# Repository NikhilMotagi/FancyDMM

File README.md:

# FancyDMM

Inspired by the Atmega328P-based voltage and current measuring device utilizing the INA266 current sensor, I aim to create a more compact and cost-effective version using the versatile ATTiny microcontroller. 
This project will involve designing a circuit to measure both voltage and current, processing the data using the ATTiny, and displaying the results on an appropriate display.
To keep the code size low, I used Bare Metal coding. 
____
## Photo Gallery

|||
|-----|------|
|||

____
## Project Inspired from

link : <https://hackaday.io/project/191203-mini-oled-panel-meter>

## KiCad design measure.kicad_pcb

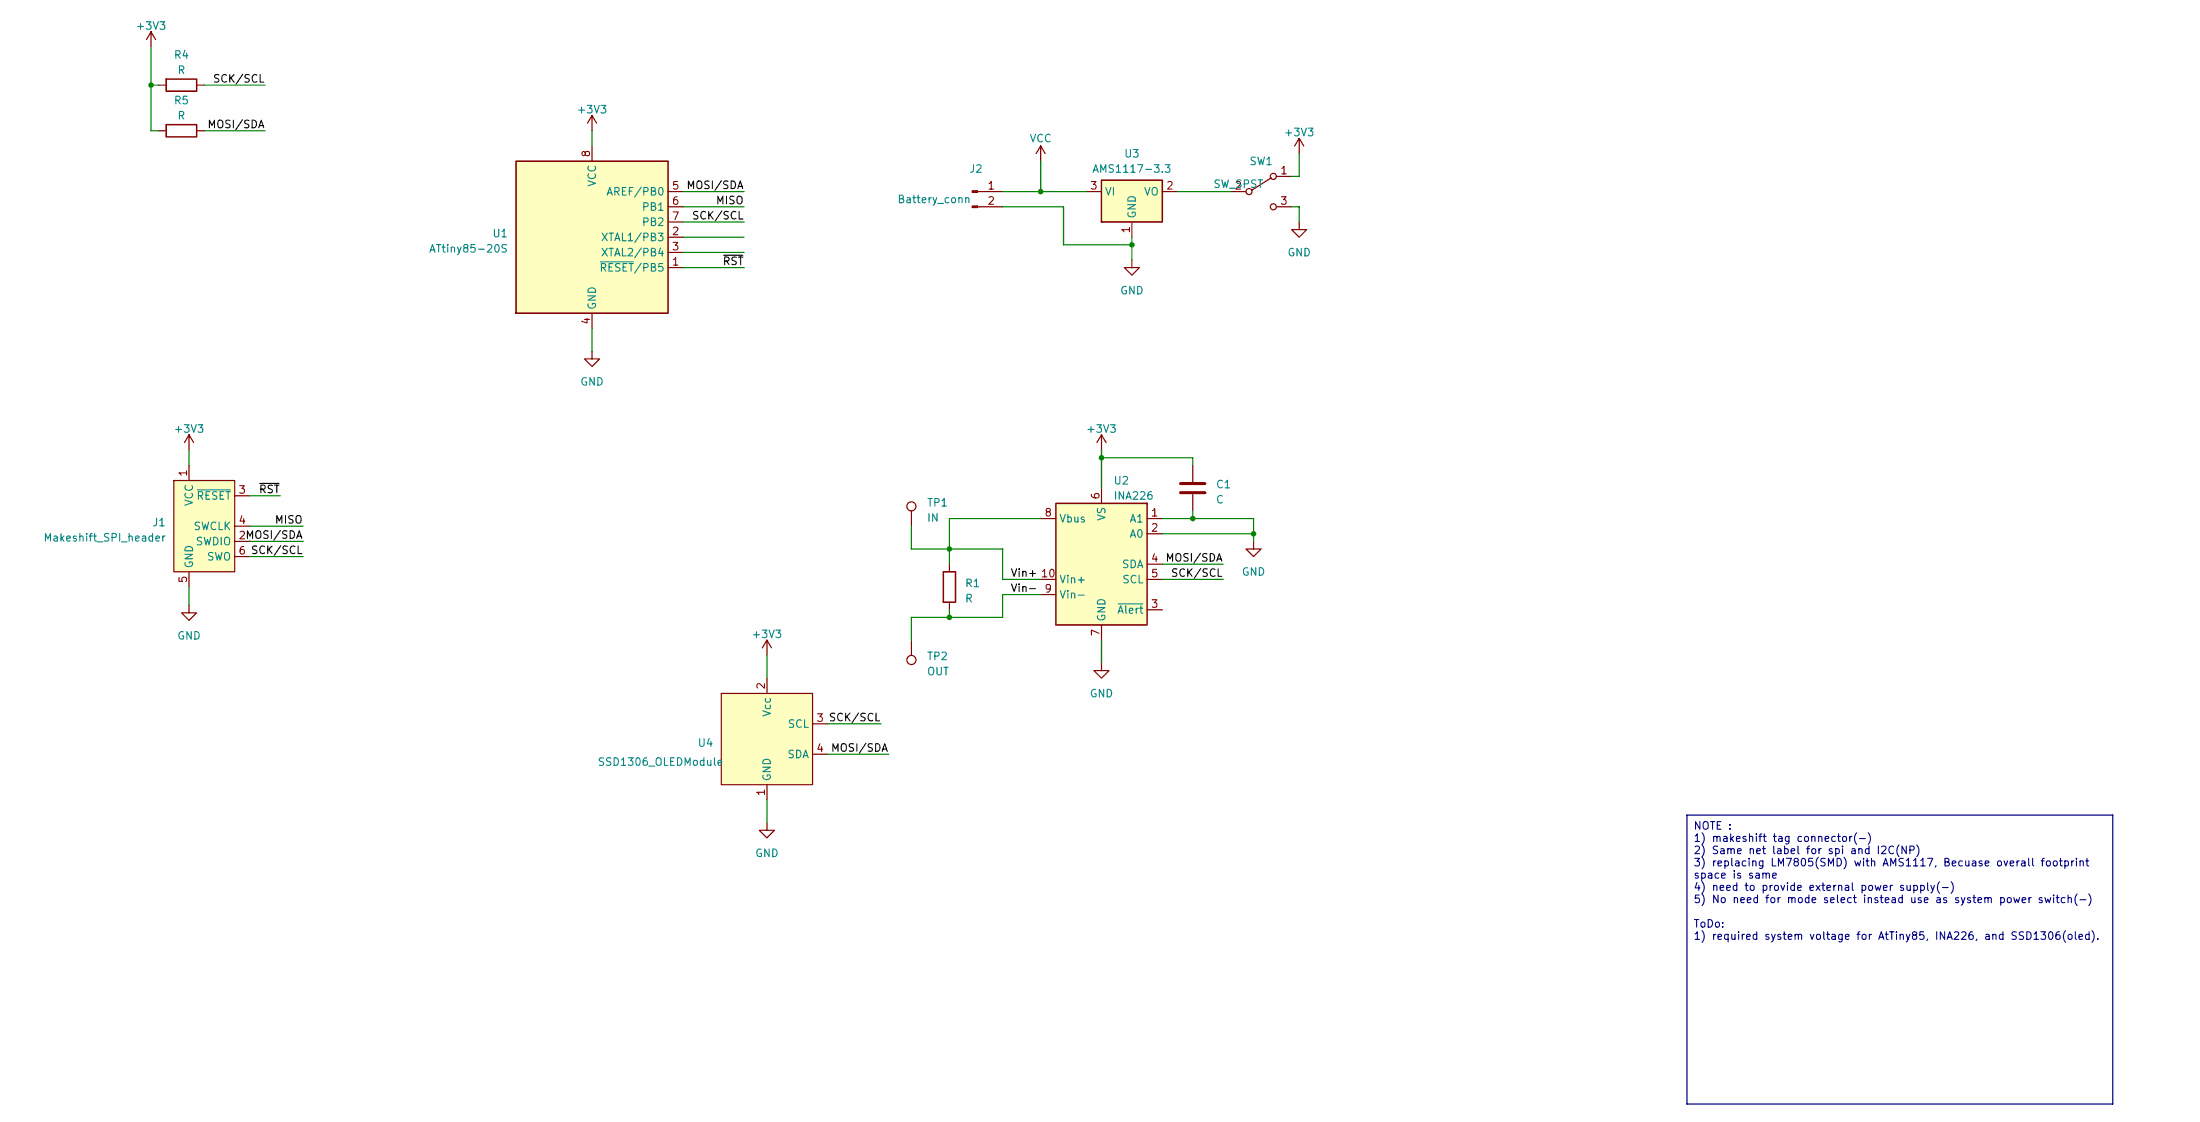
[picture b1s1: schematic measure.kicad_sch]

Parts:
C1: C; C_0805_2012Metric
J1: Makeshift_SPI_header; Tag-Connect_TC2030-IDC-NL_2x03_P1.27mm_Vertical
J2: Battery_conn; JST_GH_SM02B-GHS-TB_1x02-1MP_P1.25mm_Horizontal
R1: R; R_2512_6332Metric
R4, R5: R; R_0603_1608Metric
SW1: SW_SPST; SW_SPDT_CK-JS102011SAQN
TP1: IN; TestPoint_Pad_4.0x4.0mm
TP2: OUT; TestPoint_Pad_4.0x4.0mm
U1: ATtiny85-20S; SOIC-8W_5.3x5.3mm_P1.27mm
U2: INA226; VSSOP-10_3x3mm_P0.5mm
U3: AMS1117-3.3; SOT-223-3_TabPin2
U4: SSD1306_OLEDModule

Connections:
+3V3: C1.1, J1.1 (VCC), R4.2, R5.2, SW1.1 (A), U1.8 (VCC), U2.6 (VS), U4.2 (Vcc)
/MISO: J1.4 (SWCLK), U1.6 (PB1)
/MOSI/SDA: J1.2 (SWDIO), R5.1, U1.5 (AREF/PB0), U2.4 (SDA), U4.4 (SDA)
/SCK/SCL: J1.6 (SWO), R4.1, U1.7 (PB2), U2.5 (SCL), U4.3 (SCL)
/Vin+: R1.1, TP1.1, U2.8 (Vbus), U2.10 (Vin+)
/Vin-: R1.2, TP2.1, U2.9 (Vin-)
/~RST: J1.3 (~RESET), U1.1 (~RESET/PB5)
GND: C1.2, J1.5 (GND), J2.2, SW1.3 (C), U1.4 (GND), U2.1 (A1), U2.2 (A0), U2.7 (GND), U3.1 (GND), U4.1 (GND)
unnamed: SW1.2 (B), U3.2 (VO)
VCC: J2.1, U3.3 (VI)

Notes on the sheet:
NOTE : 1) makeshift tag connector(-) 2) Same net label for spi and I2C(NP) 3) replacing LM7805(SMD) with AMS1117, Becuase overall footprint space is same 4) need to provide external power supply(-) 5) No need for mode select instead use as system power switch(-) ToDo: 1) required system voltage for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

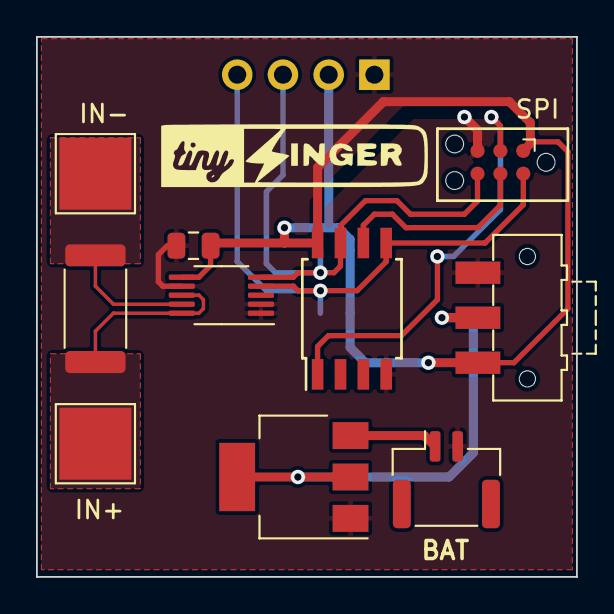
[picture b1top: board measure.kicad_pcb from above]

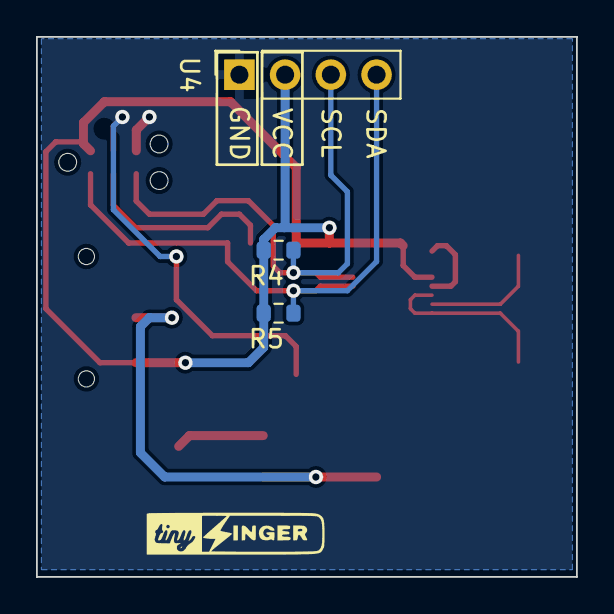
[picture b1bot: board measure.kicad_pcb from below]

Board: 2 copper layers, 30.0 x 30.0 mm, 13 parts (3 on the bottom side), 10 nets.

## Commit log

2023-06-02 no nets yet
2023-06-08 component placement
2023-06-09 Shunt looks good
2023-06-10 I2C done, new place for tiny85
2023-06-11 Lets name it tinyzinger
2024-11-27 Adding Photo gallery
2024-11-27 added assets
